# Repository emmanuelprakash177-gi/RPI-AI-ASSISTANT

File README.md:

# RPI AI ASSISTANT 

# Description 

I’m building a custom-designed AI assistant that breathes life into my desk and room. By pairing an ESP32 with a high-sensitivity INMP441 MEMS microphone, I’ve created a device that doesn't just listen, but responds through a custom 46-LED RGB ring for visually and by speaker for sound feedback.The vibrant light ring gives instant visual feedback.I think it will remove my  loneliness .The responsive companion meant to break the silence of a room.

* As i first version i want to create it in online using gemini api . 
I as a prototype.
* The 3.7V battery keeps it ready anywhere on my desk  or room .
* The next version i will create the assistant and full offline
* Using the device is as simple as a quick voice command or wake up word .

We’ve become so used to black-box devices in our homes that we’ve forgotten what it’s like to have total digital privacy.
I built this because I wanted the convenience of an AI assistant without the 'always-listening' baggage of big-tech hardware. 

###### list:
| Item                            | Description                      | Quantity | Unit_Price(USD) | Total_Price(USD) |
|---------------------------------|----------------------------------|----------|-----------------|------------------|
| Esp32 pcb                       | controlling the rpb ring and mic | 1        | $16.00          | $16.00           |
| Rgb led                         | for the RGB ring pcb             | 46       | $0.05           | $3.00            |
| INMP441 MEMS microphone module  | Plug-and-play USB mic            | 1        | $3.00           | $5.50            |
| Esp32 module                    | for esp32 pcb                    | 1        | $6.00           | $6.00            |
| 3.7v Li-Po Rechargeable Battery | Battery                          | 1        | $4.00           | $4.00            |
| Carrying Case                   | Custom-designed enclosure        | 1        | $10.00          | $10.00           |
| PCB                             | pcb and items  cost ,pcb file    | 1        | $15.00          | $15.00           |
| TOTAL PRICE                     |                                  |          |                 | $60              |

**Estimated Total Cost:** **$60**

# Files
  * 
  *

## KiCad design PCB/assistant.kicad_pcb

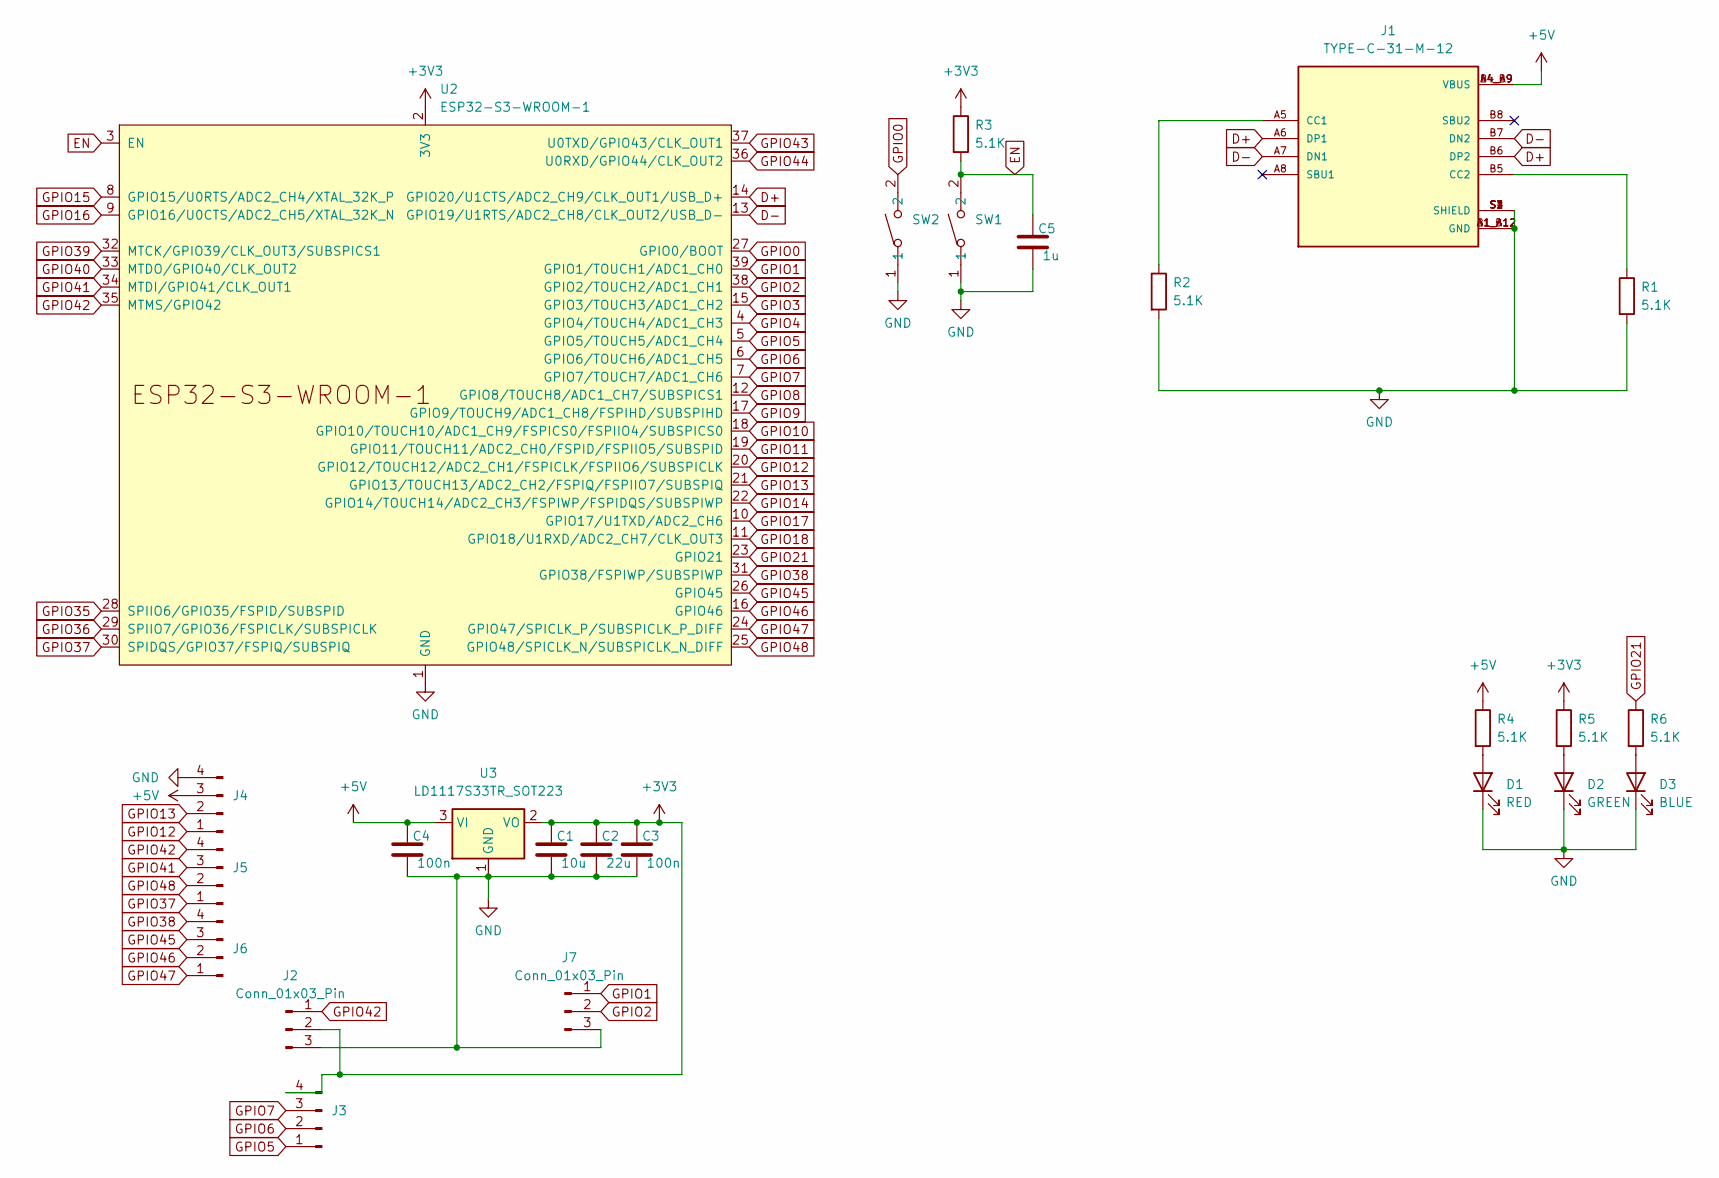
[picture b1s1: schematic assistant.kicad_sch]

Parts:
C1: 10u; C_0603_1608Metric
C2: 22u; C_0603_1608Metric
C3, C4: 100n; C_0603_1608Metric
C5: 1u; C_0603_1608Metric
D1: RED; LED_0603_1608Metric
D2: GREEN; LED_0603_1608Metric
D3: BLUE; LED_0603_1608Metric
J1: TYPE-C-31-M-12; HRO_TYPE-C-31-M-12; PARTREV 2020.12.08
J2, J7: Conn_01x03_Pin
J3, J4, J5, J6: Conn_01x04_Pin; PinSocket_1x04_P2.54mm_Vertical
R1, R2, R3, R4, R5, R6: 5.1K; R_0603_1608Metric
SW1, SW2: TS-1088-AR02016; SW-SMD_L3.9-W3.0-P4.45; LCSC Part C720477
U2: ESP32-S3-WROOM-1
U3: LD1117S33TR_SOT223; SOT-223-3_TabPin2

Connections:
+3V3: C1.1, C2.1, C3.1, J2.2, J3.4, R3.1, R5.1, U2.2 (3V3), U3.2 (VO)
+5V: C4.1, J1.A4_B9 (VBUS), J1.B4_A9 (VBUS), J4.3, R4.1, U3.3 (VI)
D+: J1.A6 (DP1), J1.B6 (DP2), U2.14 (GPIO20/U1CTS/ADC2_CH9/CLK_OUT1/USB_D+)
D-: J1.A7 (DN1), J1.B7 (DN2), U2.13 (GPIO19/U1RTS/ADC2_CH8/CLK_OUT2/USB_D-)
EN: C5.1, R3.2, SW1.2, U2.3 (EN)
GND: C1.2, C2.2, C3.2, C4.2, C5.2, D1.1 (K), D2.1 (K), D3.1 (K), J1.A1_B12 (GND), J1.B1_A12 (GND), J1.S1 (SHIELD), J1.S2 (SHIELD), J1.S3 (SHIELD), J1.S4 (SHIELD), J2.3, J4.4, J7.3, R1.2, R2.2, SW1.1, SW2.1, U2.1 (GND), U2.40 (GND), U2.41 (GND), U3.1 (GND)
GPIO0: SW2.2, U2.27 (GPIO0/BOOT)
GPIO1: J7.1, U2.39 (GPIO1/TOUCH1/ADC1_CH0)
GPIO2: J7.2, U2.38 (GPIO2/TOUCH2/ADC1_CH1)
GPIO3: U2.15 (GPIO3/TOUCH3/ADC1_CH2)
GPIO4: U2.4 (GPIO4/TOUCH4/ADC1_CH3)
GPIO5: J3.1, U2.5 (GPIO5/TOUCH5/ADC1_CH4)
GPIO6: J3.2, U2.6 (GPIO6/TOUCH6/ADC1_CH5)
GPIO7: J3.3, U2.7 (GPIO7/TOUCH7/ADC1_CH6)
GPIO8: U2.12 (GPIO8/TOUCH8/ADC1_CH7/SUBSPICS1)
GPIO9: U2.17 (GPIO9/TOUCH9/ADC1_CH8/FSPIHD/SUBSPIHD)
GPIO10: U2.18 (GPIO10/TOUCH10/ADC1_CH9/FSPICS0/FSPIIO4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)
GPIO11: U2.19 (GPIO11/TOUCH11/ADC2_CH0/FSPID/FSPIIO5/S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)
GPIO12: J4.1, U2.20 (GPIO12/TOUCH12/ADC2_CH1/FSPICLK/FSPIIO6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)
GPIO13: J4.2, U2.21 (GPIO13/TOUCH13/ADC2_CH2/FSPIQ/FSPIIO7/S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)
GPIO14: U2.22 (GPIO14/TOUCH14/ADC2_CH3/FSPIWP/FSPIDQS/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)
GPIO15: U2.8 (GPIO15/U0RTS/ADC2_CH4/XTAL_32K_P)
GPIO16: U2.9 (GPIO16/U0CTS/ADC2_CH5/XTAL_32K_N)
GPIO17: U2.10 (GPIO17/U1TXD/ADC2_CH6)
GPIO18: U2.11 (GPIO18/U1RXD/ADC2_CH7/CLK_OUT3)
GPIO21: R6.1, U2.23 (GPIO21)
GPIO35: U2.28 (SPIIO6/GPIO35/FSPID/SUBSPID)
GPIO36: U2.29 (SPIIO7/GPIO36/FSPICLK/SUBSPICLK)
GPIO37: J5.1, U2.30 (SPIDQS/GPIO37/FSPIQ/SUBSPIQ)
GPIO38: J6.4, U2.31 (GPIO38/FSPIWP/SUBSPIWP)
GPIO39: U2.32 (MTCK/GPIO39/CLK_OUT3/SUBSPICS1)
GPIO40: U2.33 (MTDO/GPIO40/CLK_OUT2)
GPIO41: J5.3, U2.34 (MTDI/GPIO41/CLK_OUT1)
GPIO42: J2.1, J5.4, U2.35 (MTMS/GPIO42)
GPIO43: U2.37 (U0TXD/GPIO43/CLK_OUT1)
GPIO44: U2.36 (U0RXD/GPIO44/CLK_OUT2)
GPIO45: J6.3, U2.26 (GPIO45)
GPIO46: J6.2, U2.16 (GPIO46)
GPIO47: J6.1, U2.24 (GPIO47/SPICLK_P/SUBSPICLK_P_DIFF)
GPIO48: J5.2, U2.25 (GPIO48/SPICLK_N/SUBSPICLK_N_DIFF)
unnamed: D1.2 (A), R4.2
unnamed: D2.2 (A), R5.2
unnamed: D3.2 (A), R6.2
unnamed: J1.A5 (CC1), R2.1
unnamed: J1.B5 (CC2), R1.1

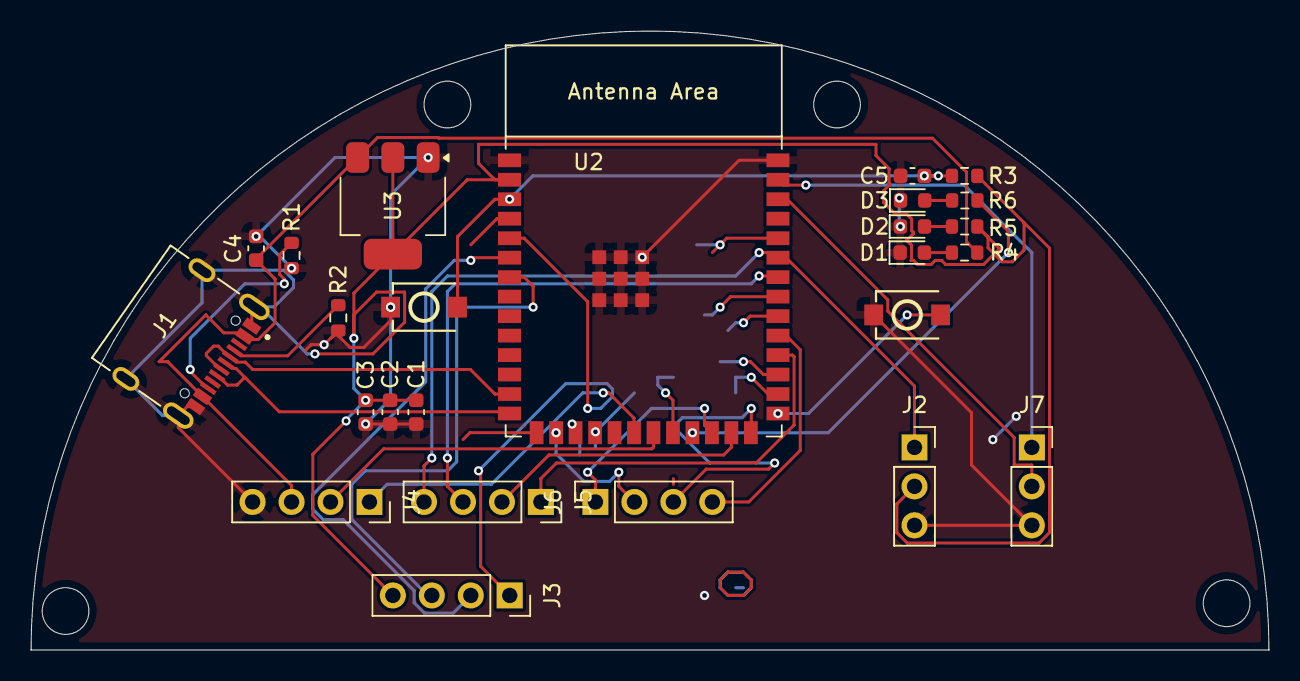
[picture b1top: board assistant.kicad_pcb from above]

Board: 2 copper layers, 80.7 x 40.4 mm, 25 parts (0 on the bottom side), 28 nets.

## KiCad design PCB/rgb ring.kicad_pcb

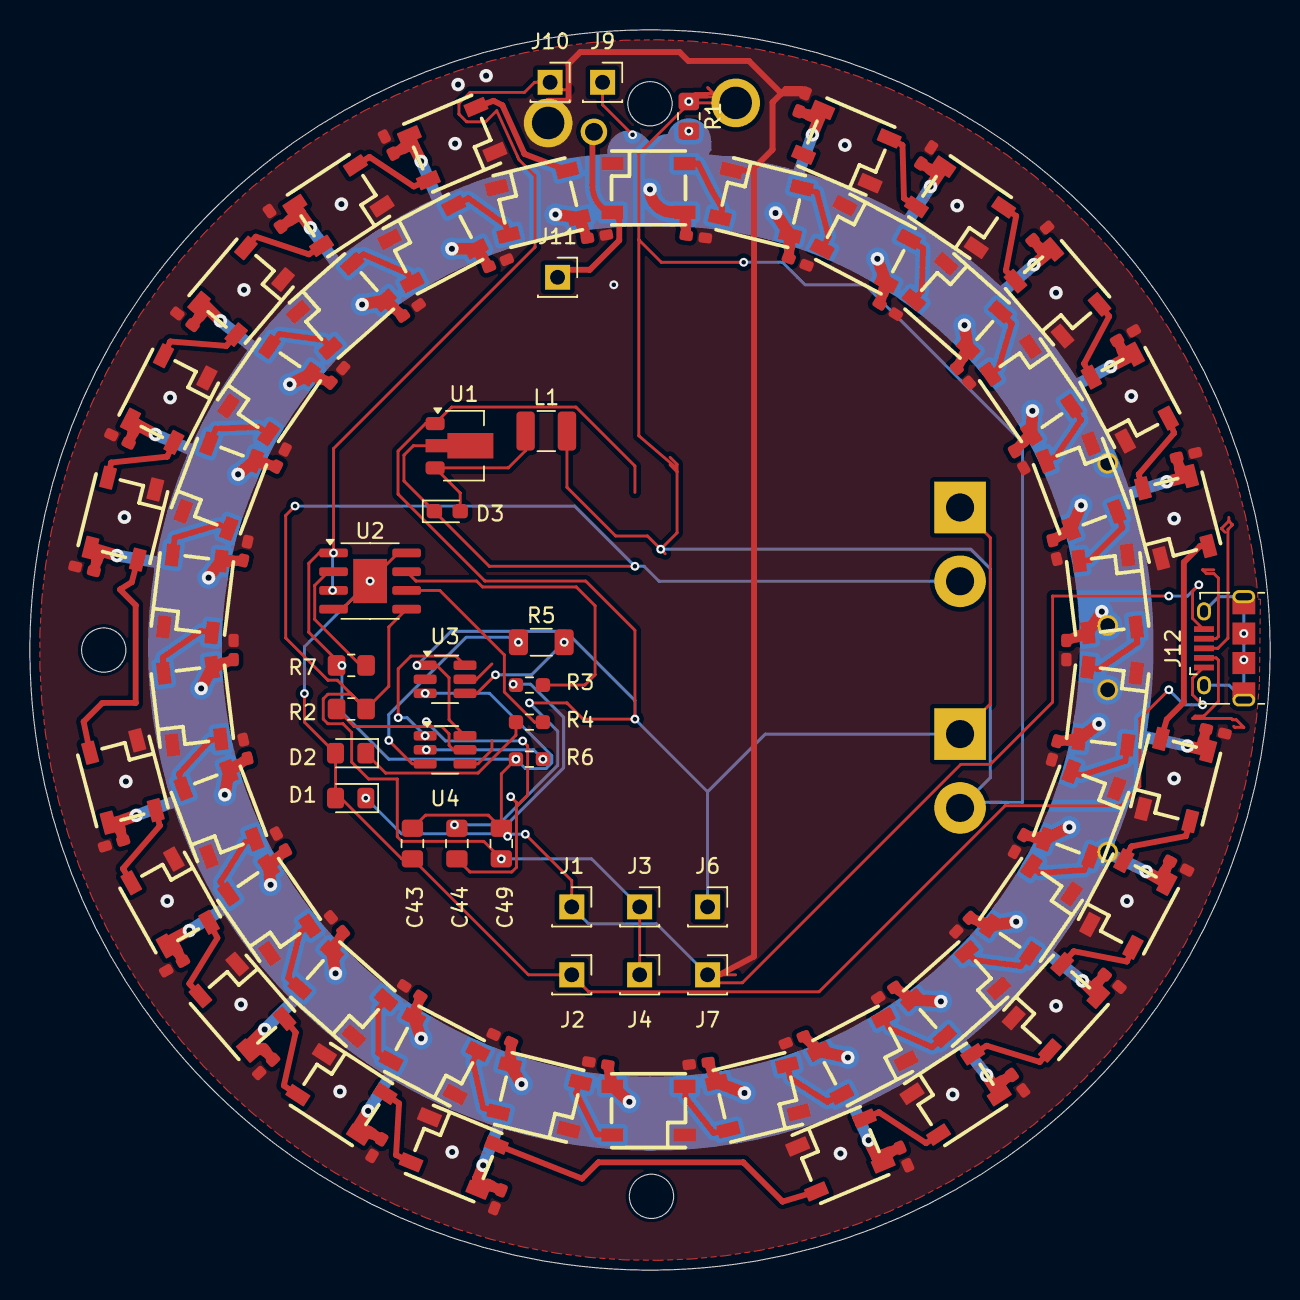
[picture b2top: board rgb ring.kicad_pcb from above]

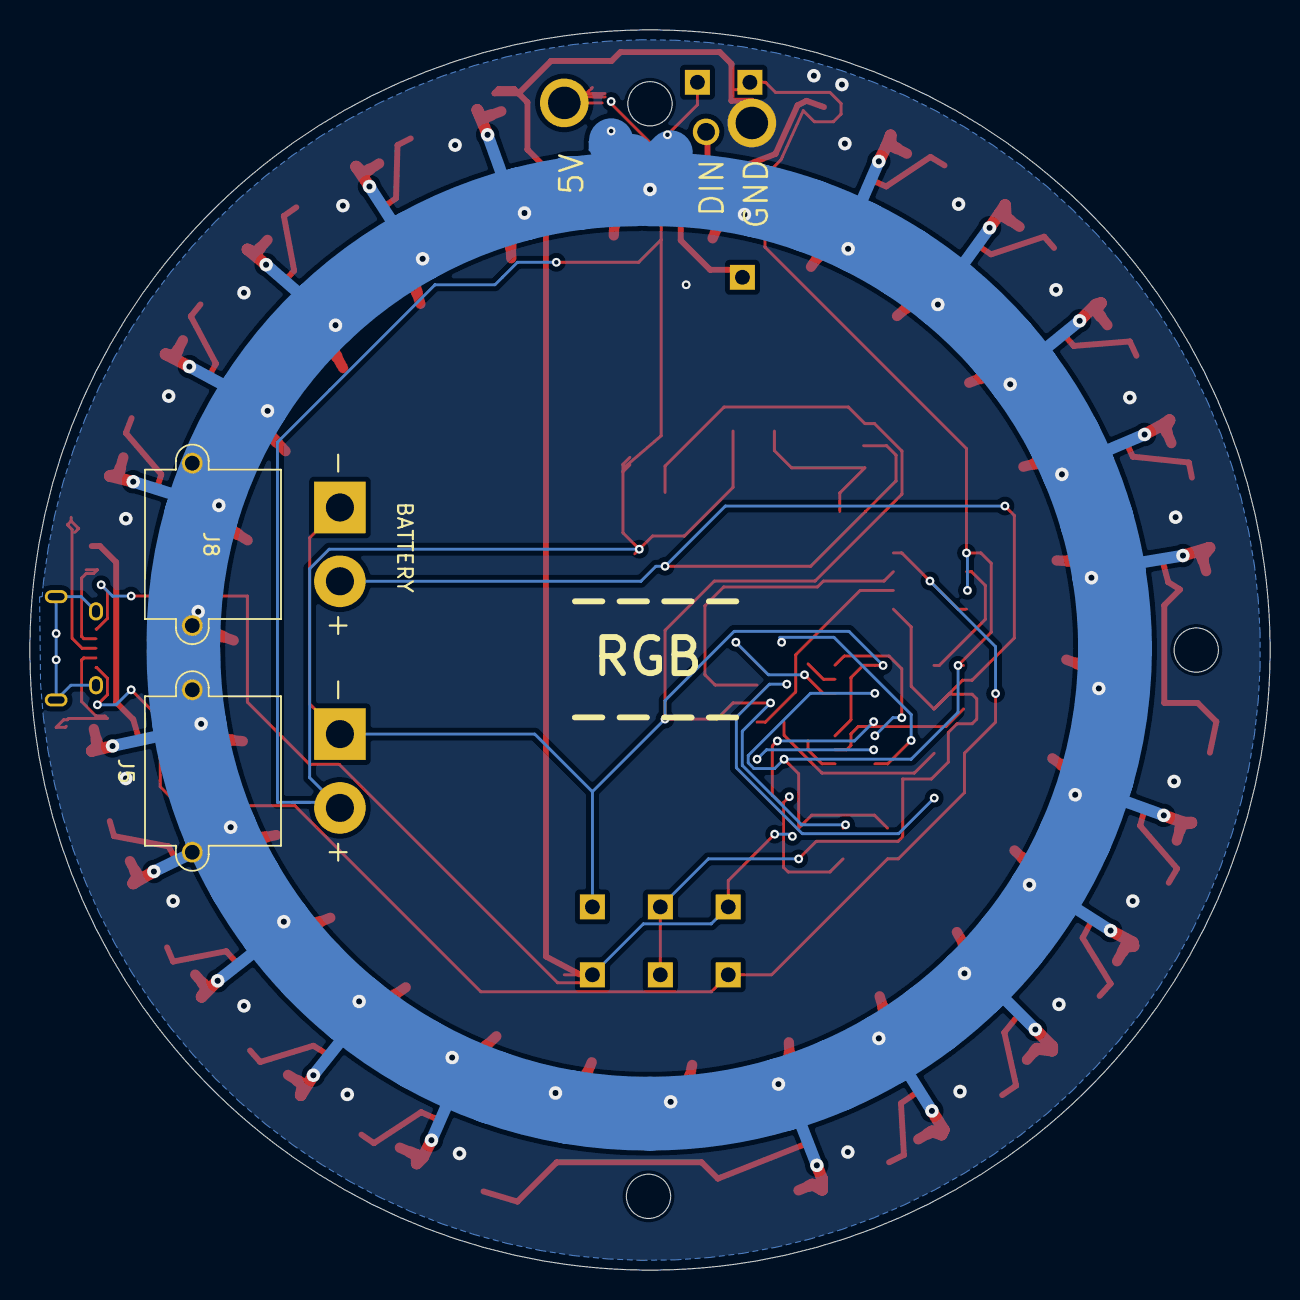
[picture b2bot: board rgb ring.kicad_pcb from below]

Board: 2 copper layers, 84.0 x 84.0 mm, 128 parts (5 on the bottom side), 65 nets.

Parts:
C1, C2, C3, C4, C5, C6, C7, C8, C9, C10, C11, C12, C13, C14, C15, C16, C17, C18, C19, C20, C21, C22, C23, C24, C25, C26, C27, C28, C29, C30, C31, C32, C33, C34, C35, C36, C37, C38, C39, C40, C41, C42, C43, C44#2, C45, C46: CAP_0603; CAP_0402
C43#2, C44: 0.1uF; C_0805_2012Metric_Pad1.18x1.45mm_HandSolder
C49: 10uF; C_0805_2012Metric_Pad1.18x1.45mm_HandSolder
D1: RED; LED_0805_2012Metric_Pad1.15x1.40mm_HandSolder
D2: GREEN; LED_0805_2012Metric_Pad1.15x1.40mm_HandSolder
D3: D; D_0603_1608Metric_Pad1.05x0.95mm_HandSolder
DIN0: SMD/RREC2.0X4.0; Lead_1.00mm
GND0: SMD/RREC2.0X4.0; Lead_2.00mm
J1, J2, J3, J4, J6, J7, J9, J10, J11: Conn_01x01_Female; PinSocket_1x01_P2.54mm_Vertical
J5, J8: Conn_01x02_Pin; AMASS_XT30PW-M_1x02_P2.50mm_Horizontal
J12: USB_B_Micro; USB_Micro-B_Amphenol_10118194_Horizontal
L1: L; L_1210_3225Metric
LED1, LED2, LED3, LED4, LED5, LED6, LED7, LED8, LED9, LED10, LED11, LED12, LED13, LED14, LED15, LED16, LED17, LED18, LED19, LED20, LED21, LED22, LED23, LED24, LED25, LED26, LED27, LED28, LED29, LED30, LED31, LED32, LED33, LED34, LED35, LED36, LED37, LED38, LED39, LED40, LED41, LED42, LED43, LED44, LED45, LED46: WS2812B
R1: R; R_0805_2012Metric_Pad1.20x1.40mm_HandSolder
R2: 100; R_0805_2012Metric_Pad1.20x1.40mm_HandSolder
R3, R4, R6: 1k; R_0603_1608Metric_Pad0.98x0.95mm_HandSolder
R5: 0R; R_1206_3216Metric_Pad1.30x1.75mm_HandSolder
R7: 10k; R_0805_2012Metric_Pad1.20x1.40mm_HandSolder
U1: L78L08_SOT89; SOT-89-3
U2: TP4056; SOIC-8-1EP_3.9x4.9mm_P1.27mm_EP2.29x3mm
U3: FS8205A; SOT-23-6_Handsoldering
U4: DW01; SOT-23-6_Handsoldering
UNK_HOLE_0: dummyfp0
UNK_HOLE_2: dummyfp2
UNK_HOLE_3: dummyfp3
V+0: SMD/RREC2.0X4.0; Lead_2.00mm

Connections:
/G1: U3.6 (G1), U4.1 (OD)
/G2: R5.2, U3.4 (G2)
/OC: R5.1, U4.3 (OC)
BAT+: C49.1, D3.1 (K), J3.1, J4.1, J8.2, R2.1, U1.2 (GND), U2.5 (BAT)
BAT-: C44.2, J5.1, J6.1, J8.1, U1.1 (OUT), U3.1 (S1), U4.6 (GND)
GND: C43#2.2, C49.2, J1.1, J7.1, J10.1, J12.5 (GND), R6.1, R7.2, U2.1 (TEMP), U2.3 (GND), U3.3 (S2)
unnamed: D1.1 (K), R3.1
unnamed: D2.1 (K), R4.1
unnamed: D3.2 (A), L1.1, U1.3 (IN)
unnamed: J5.2, L1.2
unnamed: J9.1, R1.2
unnamed: R7.1, U2.2 (PROG)
unnamed: R3.2, U2.7 (~CHRG)
unnamed: R4.2, U2.6 (~STDBY)
unnamed: R6.2, U4.2 (CS)
unnamed: C44.1, R2.2, U4.5 (VCC)
Net_0: C1.1, C2.1, C3.1, C4.1, C5.1, C6.1, C7.1, C8.1, C9.1, C10.1, C11.1, C12.1, C13.1, C14.1, C15.1, C16.1, C17.1, C18.1, C19.1, C20.1, C21.1, C22.1, C23.1, C24.1, C25.1, C26.1, C27.1, C28.1, C29.1, C30.1, C31.1, C32.1, C33.1, C34.1, C35.1, C36.1, C37.1, C38.1, C39.1, C40.1, C41.1, C42.1, C43.1, C44#2.1, C45.1, C46.1, LED1.1, LED2.1, LED3.1, LED4.1, LED5.1, LED6.1, LED7.1, LED8.1, LED9.1, LED10.1, LED11.1, LED12.1, LED13.1, LED14.1, LED15.1, LED16.1, LED17.1, LED18.1, LED19.1, LED20.1, LED21.1, LED22.1, LED23.1, LED24.1, LED25.1, LED26.1, LED27.1, LED28.1, LED29.1, LED30.1, LED31.1, LED32.1, LED33.1, LED34.1, LED35.1, LED36.1, LED37.1, LED38.1, LED39.1, LED40.1, LED41.1, LED42.1, LED43.1, LED44.1, LED45.1, LED46.1, V+0.PAD
Net_1: C1.2, C2.2, C3.2, C4.2, C5.2, C6.2, C7.2, C8.2, C9.2, C10.2, C11.2, C12.2, C13.2, C14.2, C15.2, C16.2, C17.2, C18.2, C19.2, C20.2, C21.2, C22.2, C23.2, C24.2, C25.2, C26.2, C27.2, C28.2, C29.2, C30.2, C31.2, C32.2, C33.2, C34.2, C35.2, C36.2, C37.2, C38.2, C39.2, C40.2, C41.2, C42.2, C43.2, C44#2.2, C45.2, C46.2, GND0.PAD, LED1.3, LED2.3, LED3.3, LED4.3, LED5.3, LED6.3, LED7.3, LED8.3, LED9.3, LED10.3, LED11.3, LED12.3, LED13.3, LED14.3, LED15.3, LED16.3, LED17.3, LED18.3, LED19.3, LED20.3, LED21.3, LED22.3, LED23.3, LED24.3, LED25.3, LED26.3, LED27.3, LED28.3, LED29.3, LED30.3, LED31.3, LED32.3, LED33.3, LED34.3, LED35.3, LED36.3, LED37.3, LED38.3, LED39.3, LED40.3, LED41.3, LED42.3, LED43.3, LED44.3, LED45.3, LED46.3
Net_2: LED1.2, LED2.4
Net_3: LED2.2, LED3.4
Net_4: LED3.2, LED4.4
Net_5: LED4.2, LED5.4
Net_6: LED5.2, LED6.4
Net_7: LED6.2, LED7.4
Net_8: LED7.2, LED8.4
Net_9: LED8.2, LED9.4
Net_10: LED9.2, LED10.4
Net_11: LED19.2, LED20.4
Net_12: LED18.2, LED19.4
Net_13: LED17.2, LED18.4
Net_14: LED16.2, LED17.4
Net_15: LED15.2, LED16.4
Net_16: LED14.2, LED15.4
Net_17: LED13.2, LED14.4
Net_18: LED12.2, LED13.4
Net_19: LED11.2, LED12.4
Net_20: LED21.2, LED22.4
Net_21: LED22.2, LED23.4
Net_22: LED23.2, LED24.4
Net_23: LED24.2, LED25.4
Net_24: LED25.2, LED26.4
Net_25: LED26.2, LED27.4
Net_26: LED27.2, LED28.4
Net_27: LED28.2, LED29.4
Net_28: LED29.2, LED30.4
Net_29: LED39.2, LED40.4
Net_30: LED38.2, LED39.4
Net_31: LED37.2, LED38.4
Net_32: LED36.2, LED37.4
Net_33: LED35.2, LED36.4
Net_34: LED34.2, LED35.4
Net_35: LED33.2, LED34.4
Net_36: LED32.2, LED33.4
Net_37: LED31.2, LED32.4
Net_38: LED10.2, LED11.4
Net_39: LED20.2, LED21.4
Net_40: DIN0.PAD, LED1.4
Net_44: LED45.2, LED46.4
Net_45: LED44.2, LED45.4
Net_46: LED43.2, LED44.4
Net_47: LED42.2, LED43.4
Net_48: LED41.2, LED42.4
Net_49: LED30.2, LED31.4
Net_50: LED40.2, LED41.4
VIN: C43#2.1, D1.2 (A), D2.2 (A), J2.1, J12.1 (VBUS), U2.4 (VCC), U2.8 (CE), U2.9 (PP)

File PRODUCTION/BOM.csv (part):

Designator,Comment,Package,Mid X,Mid Y,Rotation,Layer
"DIN0","SMD/RREC2.0X4.0","Lead_1.00mm",144.701100,-69.903600,-90.000000,bottom
"GND0","SMD/RREC2.0X4.0","Lead_2.00mm",141.601100,-69.303600,-90.000000,bottom
"J5","Conn_01x02_Pin","AMASS_XT30PW-M_1x02_P2.50mm_Horizontal",169.501100,-110.696000,90.000000,bottom
"J8","Conn_01x02_Pin","AMASS_XT30PW-M_1x02_P2.50mm_Horizontal",169.501100,-95.346000,90.000000,bottom
"V+0","SMD/RREC2.0X4.0","Lead_2.00mm",154.305000,-67.945000,-90.000000,bottom
"C1","CAP_0603","CAP_0402",167.201100,-71.503600,56.826796,top
"C2","CAP_0603","CAP_0402",138.201100,-142.203600,-111.554041,top
"C3","CAP_0603","CAP_0402",169.701100,-86.403600,-49.789191,top
"C4","CAP_0603","CAP_0402",158.501100,-78.703600,-21.295999,top
"C5","CAP_0603","CAP_0402",164.601100,-81.903600,-32.342626,top
"C6","CAP_0603","CAP_0402",173.501100,-92.103600,-61.019163,top
"C7","CAP_0603","CAP_0402",175.901100,-98.203600,-76.718207,top
"C8","CAP_0603","CAP_0402",176.701100,-105.003600,-89.804563,top
"C9","CAP_0603","CAP_0402",184.801100,-91.803600,13.544722,top
"C10","CAP_0603","CAP_0402",175.901100,-111.803600,-106.030728,top
"C11","CAP_0603","CAP_0402",179.801100,-127.403600,-39.836914,top
"C12","CAP_0603","CAP_0402",173.401100,-134.303600,-53.880109,top
"C13","CAP_0603","CAP_0402",165.701100,-139.303600,-66.531017,top
"C14","CAP_0603","CAP_0402",138.501100,-131.303600,155.770036,top
"C15","CAP_0603","CAP_0402",145.001100,-133.003600,170.804448,top
"C16","CAP_0603","CAP_0402",151.801100,-133.003600,-173.049601,top
"C17","CAP_0603","CAP_0402",158.301100,-131.403600,-158.668360,top
"C18","CAP_0603","CAP_0402",164.501100,-128.203600,-146.848241,top
"C19","CAP_0603","CAP_0402",169.701100,-123.603600,-134.168685,top
"C20","CAP_0603","CAP_0402",173.501100,-118.103600,-119.031140,top
"C21","CAP_0603","CAP_0402",184.301100,-119.603600,-27.862096,top
"C22","CAP_0603","CAP_0402",174.901100,-76.803600,40.142265,top
"C23","CAP_0603","CAP_0402",180.701100,-83.703600,29.427954,top
"C24","CAP_0603","CAP_0402",132.301100,-82.003600,35.076476,top
"C25","CAP_0603","CAP_0402",151.601100,-77.003600,-7.321559,top
"C26","CAP_0603","CAP_0402",158.801100,-67.903600,69.133929,top
"C27","CAP_0603","CAP_0402",144.901100,-77.003600,9.975195,top
"C28","CAP_0603","CAP_0402",138.201100,-78.803600,21.858340,top
"C29","CAP_0603","CAP_0402",130.801100,-70.803600,116.809748,top
"C30","CAP_0603","CAP_0402",123.101100,-75.803600,124.716565,top
"C31","CAP_0603","CAP_0402",122.501100,-133.203600,-136.420409,top
"C32","CAP_0603","CAP_0402",112.601100,-90.703600,154.063463,top
"C33","CAP_0603","CAP_0402",110.201100,-99.503600,165.901613,top
"C34","CAP_0603","CAP_0402",112.201100,-118.103600,-162.719172,top
"C35","CAP_0603","CAP_0402",127.301100,-123.603600,129.689839,top
"C36","CAP_0603","CAP_0402",132.401100,-128.103600,147.182240,top
"C37","CAP_0603","CAP_0402",186.801100,-110.503600,-13.784523,top
"C38","CAP_0603","CAP_0402",116.301100,-126.403600,-150.360472,top
"C39","CAP_0603","CAP_0402",130.001100,-138.703600,-120.446346,top
"C40","CAP_0603","CAP_0402",117.001100,-82.603600,142.518364,top
"C41","CAP_0603","CAP_0402",127.301100,-86.403600,49.474906,top
"C42","CAP_0603","CAP_0402",123.501100,-92.003600,63.426428,top
"C43","CAP_0603","CAP_0402",121.101100,-98.303600,77.212634,top
"C43","0.1uF","C_0805_2012Metric_Pad1.18x1.45mm_HandSolder",132.410000,-118.110000,90.000000,top
"C44","CAP_0603","CAP_0402",121.101100,-111.703600,103.144704,top
"C44","0.1uF","C_0805_2012Metric_Pad1.18x1.45mm_HandSolder",135.420000,-118.110000,90.000000,top
"C45","CAP_0603","CAP_0402",123.501100,-118.003600,118.574457,top
"C46","CAP_0603","CAP_0402",120.301100,-105.003600,90.006782,top
"C49","10uF","C_0805_2012Metric_Pad1.18x1.45mm_HandSolder",138.430000,-118.110000,90.000000,top
"D1","RED","LED_0805_2012Metric_Pad1.15x1.40mm_HandSolder",128.225000,-115.030000,180.000000,top
"D2","GREEN","LED_0805_2012Metric_Pad1.15x1.40mm_HandSolder",128.225000,-111.990000,180.000000,top
"D3","D","D_0603_1608Metric_Pad1.05x0.95mm_HandSolder",134.770000,-95.610000,0.000000,top
"J1","Conn_01x01_Female","PinSocket_1x01_P2.54mm_Vertical",143.200000,-122.400000,0.000000,top
"J2","Conn_01x01_Female","PinSocket_1x01_P2.54mm_Vertical",143.200000,-127.000000,0.000000,top
"J3","Conn_01x01_Female","PinSocket_1x01_P2.54mm_Vertical",147.800000,-122.400000,0.000000,top
"J4","Conn_01x01_Female","PinSocket_1x01_P2.54mm_Vertical",147.800000,-127.000000,0.000000,top
"J6","Conn_01x01_Female","PinSocket_1x01_P2.54mm_Vertical",152.400000,-122.400000,0.000000,top
"J7","Conn_01x01_Female","PinSocket_1x01_P2.54mm_Vertical",152.400000,-127.000000,0.000000,top
"J9","Conn_01x01_Female","PinSocket_1x01_P2.54mm_Vertical",145.288000,-66.548000,0.000000,top
"J10","Conn_01x01_Female","PinSocket_1x01_P2.54mm_Vertical",141.732000,-66.548000,0.000000,top
"J11","Conn_01x01_Female","PinSocket_1x01_P2.54mm_Vertical",142.240000,-79.756000,0.000000,top
"J12","USB_B_Micro","USB_Micro-B_Amphenol_10118194_Horizontal",187.422000,-104.886000,90.000000,top
"L1","L","L_1210_3225Metric",141.475000,-90.170000,0.000000,top
"LED1","WS2812B","WS2812B",148.401100,-73.703600,180.000000,top
"LED2","WS2812B","WS2812B",156.001100,-74.703600,166.158602,top
"LED3","WS2812B","WS2812B",163.101100,-77.503600,152.310213,top
"LED4","WS2812B","WS2812B",169.301100,-81.703600,138.467552,top
"LED5","WS2812B","WS2812B",174.301100,-87.403600,124.619162,top
"LED6","WS2812B","WS2812B",177.701100,-93.903600,110.770772,top
"LED7","WS2812B","WS2812B",179.501100,-101.203600,96.928112,top
"LED8","WS2812B","WS2812B",179.501100,-108.803600,83.079722,top
"LED9","WS2812B","WS2812B",177.701100,-116.103600,69.242791,top
"LED10","WS2812B","WS2812B",174.301100,-122.603600,55.388672,top
"LED11","WS2812B","WS2812B",169.201100,-128.303600,41.540282,top
"LED12","WS2812B","WS2812B",162.901100,-132.503600,27.697622,top
"LED13","WS2812B","WS2812B",155.801100,-135.303600,13.849232,top
"LED14","WS2812B","WS2812B",148.401100,-136.203600,0.000000,top
"LED15","WS2812B","WS2812B",141.001100,-135.303600,-13.847548,top
"LED16","WS2812B","WS2812B",133.901100,-132.503600,-27.701668,top
"LED17","WS2812B","WS2812B",127.701100,-128.303600,-41.538598,top
"LED18","WS2812B","WS2812B",122.701100,-122.603600,-55.392718,top
"LED19","WS2812B","WS2812B",119.301100,-116.103600,-69.241108,top
"LED20","WS2812B","WS2812B",117.501100,-108.803600,-83.078038,top
"LED21","WS2812B","WS2812B",117.501100,-101.203600,-96.932158,top
"LED22","WS2812B","WS2812B",119.301100,-93.903600,-110.769089,top
"LED23","WS2812B","WS2812B",122.701100,-87.403600,-124.617479,top
"LED24","WS2812B","WS2812B",127.601100,-81.703600,-138.471598,top
"LED25","WS2812B","WS2812B",133.801100,-77.503600,-152.308529,top
"LED26","WS2812B","WS2812B",140.901100,-74.703600,-166.162648,top
"LED27","WS2812B","WS2812B",135.101100,-70.703600,22.975608,top
"LED28","WS2812B","WS2812B",127.401100,-74.903600,33.191445,top
"LED29","WS2812B","WS2812B",120.801100,-80.703600,49.641063,top
"LED30","WS2812B","WS2812B",115.901100,-88.003600,62.847741,top
"LED31","WS2812B","WS2812B",112.801100,-96.103600,75.968474,top
"LED32","WS2812B","WS2812B",112.801100,-113.903600,104.817741,top
"LED33","WS2812B","WS2812B",116.001100,-122.103600,119.124497,top
"LED34","WS2812B","WS2812B",120.901100,-129.203600,130.921698,top
"LED35","WS2812B","WS2812B",127.601100,-135.103600,146.970246,top
"LED36","WS2812B","WS2812B",135.201100,-139.103600,157.678827,top
"LED37","WS2812B","WS2812B",161.401100,-139.203600,-157.276073,top
"LED38","WS2812B","WS2812B",169.201100,-135.103600,-146.985751,top
"LED39","WS2812B","WS2812B",176.001100,-129.203600,-132.020093,top
"LED40","WS2812B","WS2812B",180.901100,-122.203600,-117.948250,top
"LED41","WS2812B","WS2812B",184.101100,-113.803600,-104.357691,top
"LED42","WS2812B","WS2812B",184.101100,-96.003600,-75.406134,top
"LED43","WS2812B","WS2812B",181.001100,-87.903600,-62.004651,top
"LED44","WS2812B","WS2812B",176.101100,-80.803600,-49.433957,top
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
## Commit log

2026-01-04 Rename WhatsApp Image 2026-01-04 at 11.45.28 AM.jpeg to RGB ring
2026-01-04 Rename RGB ring to RGB ring.jpeg
2026-01-05 Create 3D model
2026-01-15 Rename rgb ring.pdf to layers.pdf
2026-01-15 Rename Screenshot from 2026-01-15 16-06-53.png to Base.png
2026-01-23 Rename rgb ring.png to Schematic.png
2026-01-23 Rename Screenshot from 2026-01-15 14-50-12.png to Layer.png
2026-01-23 Rename Screenshot from 2026-01-15 14-53-30.png to PCB.png
2026-01-23 Rename gerber.zip to assistant_gerber.zip
2026-03-22 Rename BOM (1).csv to BOM.csv
2026-03-22 Rename Screenshot from 2026-01-23 20-41-59.png to assistant_pcb.png
2026-03-22 Rename Screenshot from 2026-01-23 20-41-39.png to assistant_layer.png
2026-04-02 Rename BOM.csv to pcb.csv
